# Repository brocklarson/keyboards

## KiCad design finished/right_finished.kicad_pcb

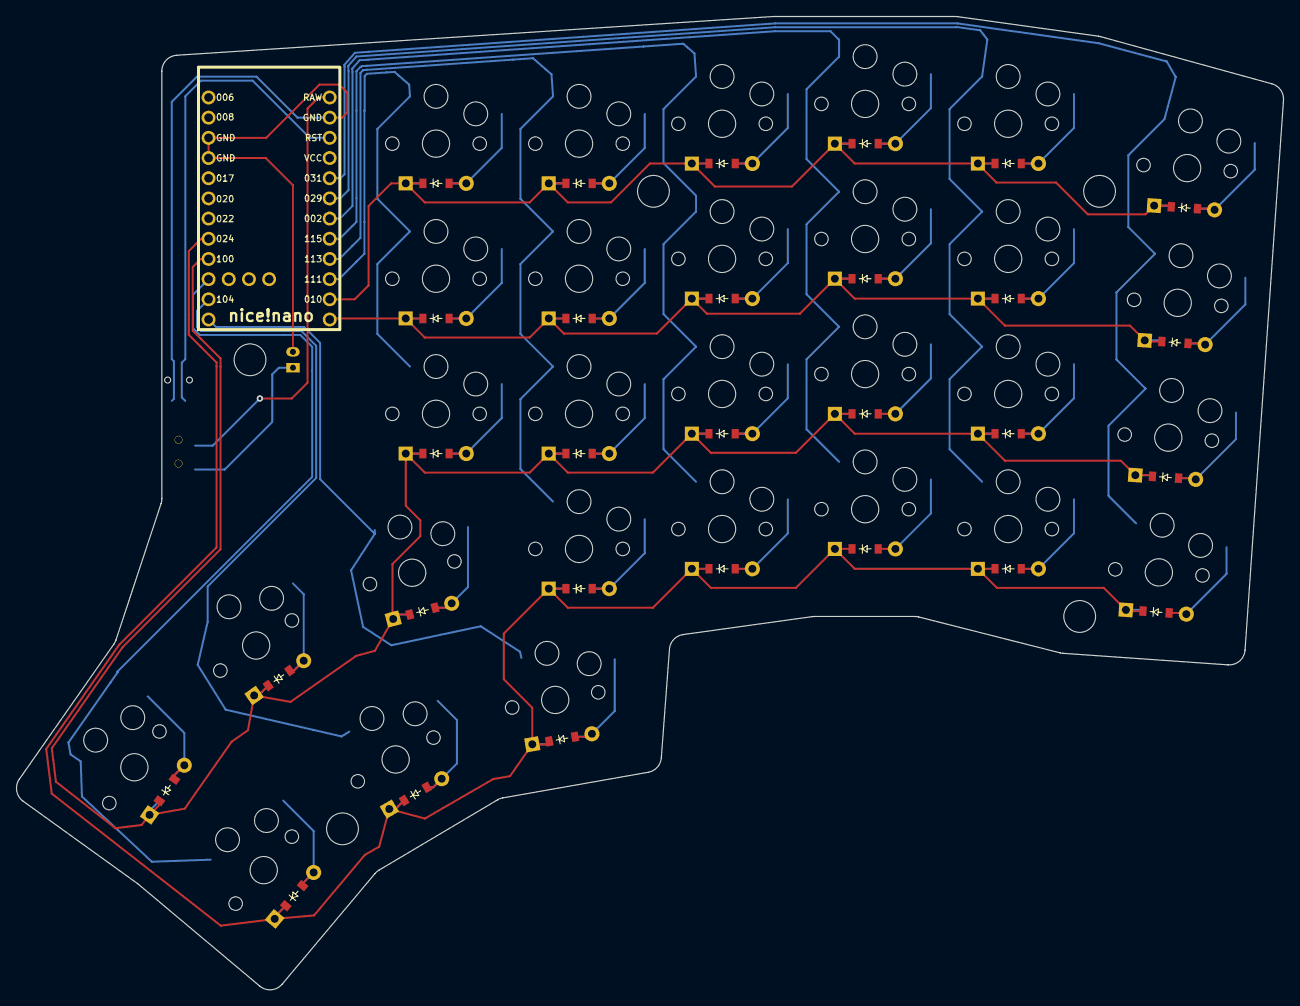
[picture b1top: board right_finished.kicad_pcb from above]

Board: 2 copper layers, 159.4 x 122.5 mm, 62 parts (0 on the bottom side), 46 nets.

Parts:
B1: Panasonic_EVQPUL_EVQPUC
D1, D2, D3, D4, D5, D6, D7, D8, D9, D10, D11, D12, D13, D14, D15, D16, D17, D18, D19, D20, D21, D22, D23, D24, D25, D26, D27, D28, D29: ComboDiode
JST1: JST_PH_S2B-PH-K_02x2.00mm_Angled
MCU1: nice_nano
S1, S2, S3, S4, S5, S6, S7, S8, S9, S10, S11, S12, S13, S14, S15, S16, S17, S18, S19, S20, S21, S22, S23, S24, S25, S26, S27, S28, S29: PG1350
T1: SPDT_C128955

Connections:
GND: B1.1, JST1.2, MCU1.3, MCU1.4, MCU1.23
P002: MCU1.18, S9.1, S10.1, S11.1, S12.1
P009: D3.1, D7.1, D11.1, D15.1, D19.1, D22.1, MCU1.13
P010: D4.1, D8.1, D12.1, D16.1, D20.1, D23.1, MCU1.14
P011: MCU1.10, S26.1, S29.1
P024: D1.1, D5.1, D9.1, D13.1, D17.1, D24.1, D25.1, D26.1, MCU1.8
P029: MCU1.19, S5.1, S6.1, S7.1, S8.1
P031: MCU1.20, S1.1, S2.1, S3.1, S4.1
P100: D2.1, D6.1, D10.1, D14.1, D18.1, D21.1, D27.1, D28.1, D29.1, MCU1.9
P104: MCU1.11, S25.1, S28.1
P106: MCU1.12, S24.1, S27.1
P111: MCU1.15, S21.1, S22.1, S23.1
P113: MCU1.16, S17.1, S18.1, S19.1, S20.1
P115: MCU1.17, S13.1, S14.1, S15.1, S16.1
RAW: MCU1.24, T1.2
RST: B1.2, MCU1.22
mirror_extras_home: D21.2, S21.2
mirror_extras_num: D23.2, S23.2
mirror_extras_top: D22.2, S22.2
mirror_far_thumbbottom: D26.2, S26.2
mirror_far_thumbupper: D29.2, S29.2
mirror_home_thumbbottom: D25.2, S25.2
mirror_home_thumbupper: D28.2, S28.2
mirror_index_bottom: D13.2, S13.2
mirror_index_home: D14.2, S14.2
mirror_index_num: D16.2, S16.2
mirror_index_top: D15.2, S15.2
mirror_inner_bottom: D17.2, S17.2
mirror_inner_home: D18.2, S18.2
mirror_inner_num: D20.2, S20.2
mirror_inner_top: D19.2, S19.2
mirror_middle_bottom: D9.2, S9.2
mirror_middle_home: D10.2, S10.2
mirror_middle_num: D12.2, S12.2
mirror_middle_top: D11.2, S11.2
mirror_near_thumbbottom: D24.2, S24.2
mirror_near_thumbupper: D27.2, S27.2
mirror_pinky_bottom: D1.2, S1.2
mirror_pinky_home: D2.2, S2.2
mirror_pinky_num: D4.2, S4.2
mirror_pinky_top: D3.2, S3.2
mirror_ring_bottom: D5.2, S5.2
mirror_ring_home: D6.2, S6.2
mirror_ring_num: D8.2, S8.2
mirror_ring_top: D7.2, S7.2
pos: JST1.1, T1.1

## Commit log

2024-08-24 Initial commit with config.yaml
2024-08-24 Add nice nano footprint
2024-09-16 Add pcb and cases
2024-09-26 Adjust measurements and mounting holes
2024-09-26 Adjust mounting and cases
2024-09-27 Cleanup outlines
2024-10-18 Add finished pcd and cases
